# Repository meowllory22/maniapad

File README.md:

# maniapad
macropad for 4key rhythm games like osumania, quaver, etc ! :-) also its cat shaped because why not?

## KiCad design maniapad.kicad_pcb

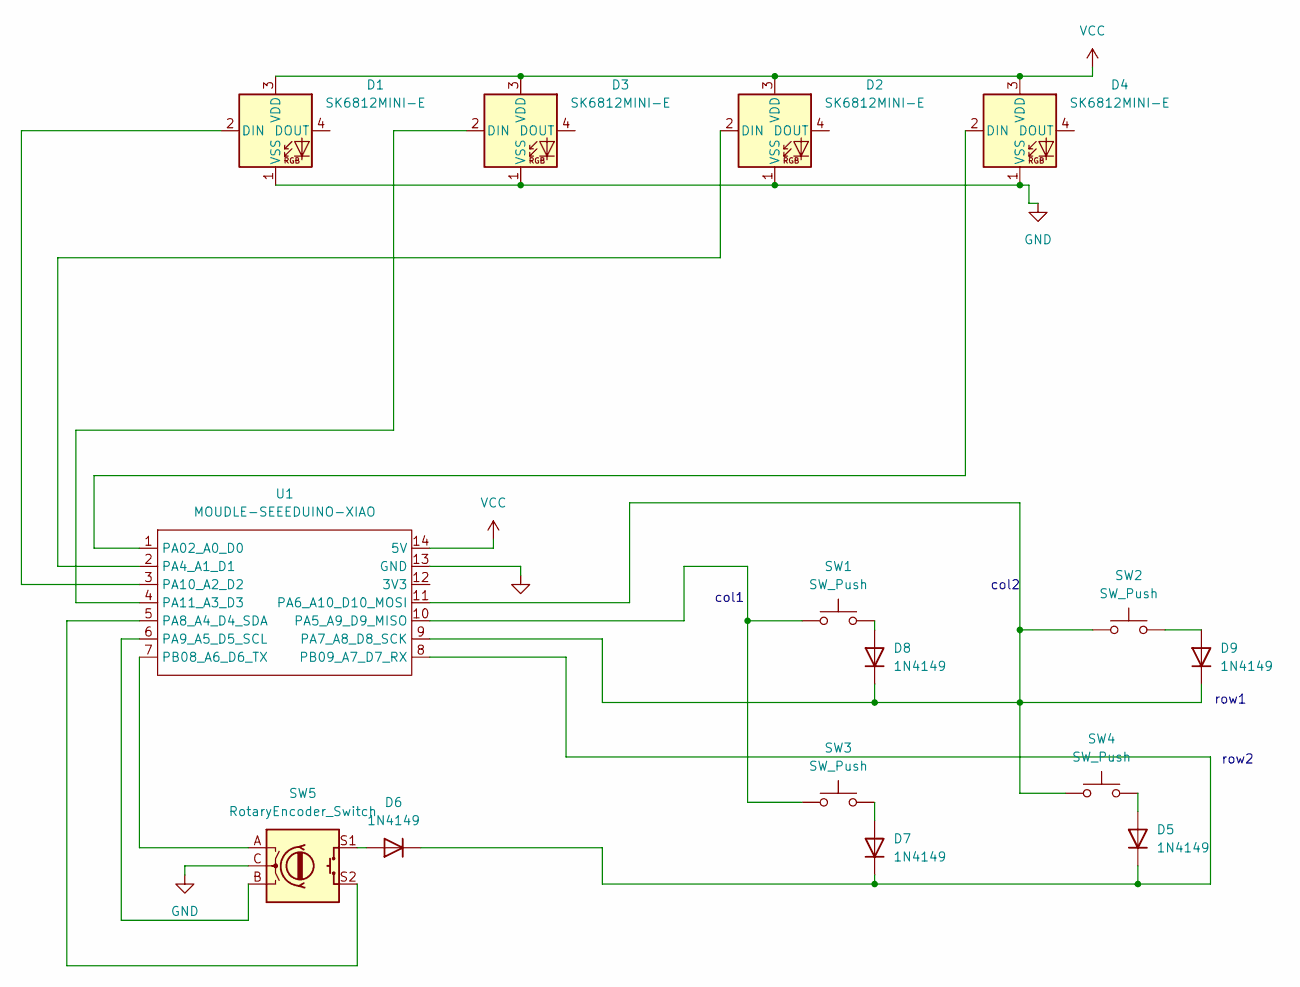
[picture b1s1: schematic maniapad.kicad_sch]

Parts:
D1, D2, D3, D4: SK6812MINI-E; LED_SK6812MINI-E_3.2x2.8mm_P1.5mm_ReverseMount
D5, D6, D7, D8, D9: 1N4149; D_DO-35_SOD27_P7.62mm_Horizontal
SW1, SW2, SW3, SW4: SW_Push; SW_Cherry_MX_1.00u_PCB
SW5: RotaryEncoder_Switch; RotaryEncoder_Alps_EC11E-Switch_Vertical_H20mm
U1: MOUDLE-SEEEDUINO-XIAO; XIAO-Generic-Hybrid-14P-2.54-21X17.8MM

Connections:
GND: D1.1 (VSS), D2.1 (VSS), D3.1 (VSS), D4.1 (VSS), SW5.C, U1.13 (GND)
unnamed: D1.2 (DIN), U1.3 (PA10_A2_D2)
unnamed: D2.2 (DIN), U1.2 (PA4_A1_D1)
unnamed: D3.2 (DIN), U1.4 (PA11_A3_D3)
unnamed: D4.2 (DIN), U1.1 (PA02_A0_D0)
unnamed: D5.2 (A), SW4.2
unnamed: D5.1 (K), D6.1 (K), D7.1 (K), U1.8 (PB09_A7_D7_RX)
unnamed: D6.2 (A), SW5.S1
unnamed: D7.2 (A), SW3.2
unnamed: D8.2 (A), SW1.2
unnamed: D8.1 (K), D9.1 (K), SW2.1, SW4.1, U1.9 (PA7_A8_D8_SCK), U1.11 (PA6_A10_D10_MOSI)
unnamed: D9.2 (A), SW2.2
unnamed: SW1.1, SW3.1, U1.10 (PA5_A9_D9_MISO)
unnamed: SW5.S2, U1.5 (PA8_A4_D4_SDA)
unnamed: SW5.B, U1.6 (PA9_A5_D5_SCL)
unnamed: SW5.A, U1.7 (PB08_A6_D6_TX)
VCC: D1.3 (VDD), D2.3 (VDD), D3.3 (VDD), D4.3 (VDD), U1.14 (5V)

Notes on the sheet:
row2
row1
col2
col1

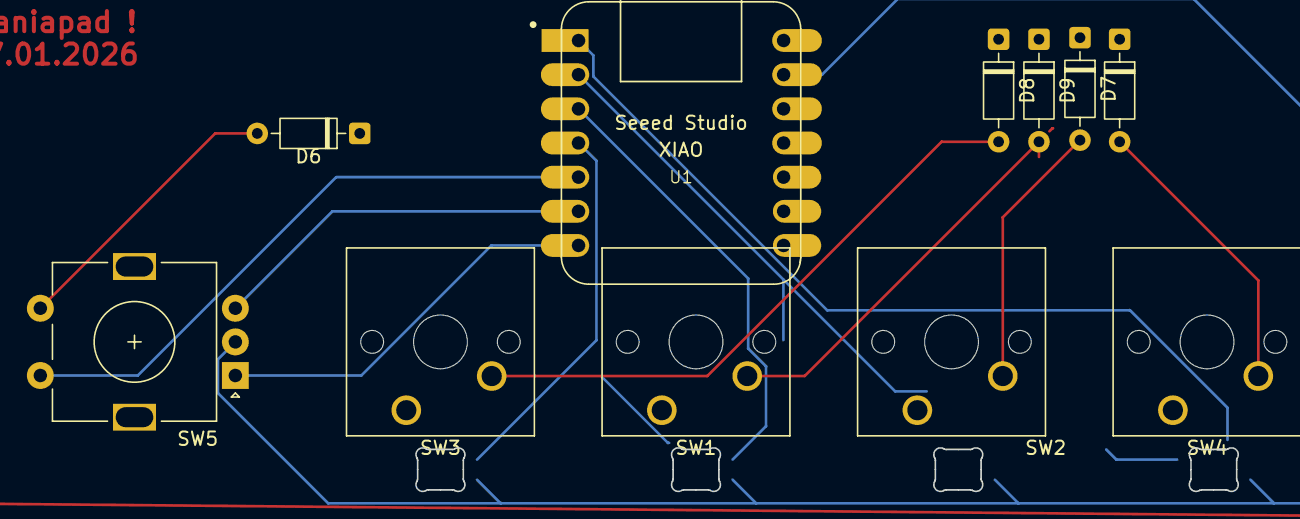
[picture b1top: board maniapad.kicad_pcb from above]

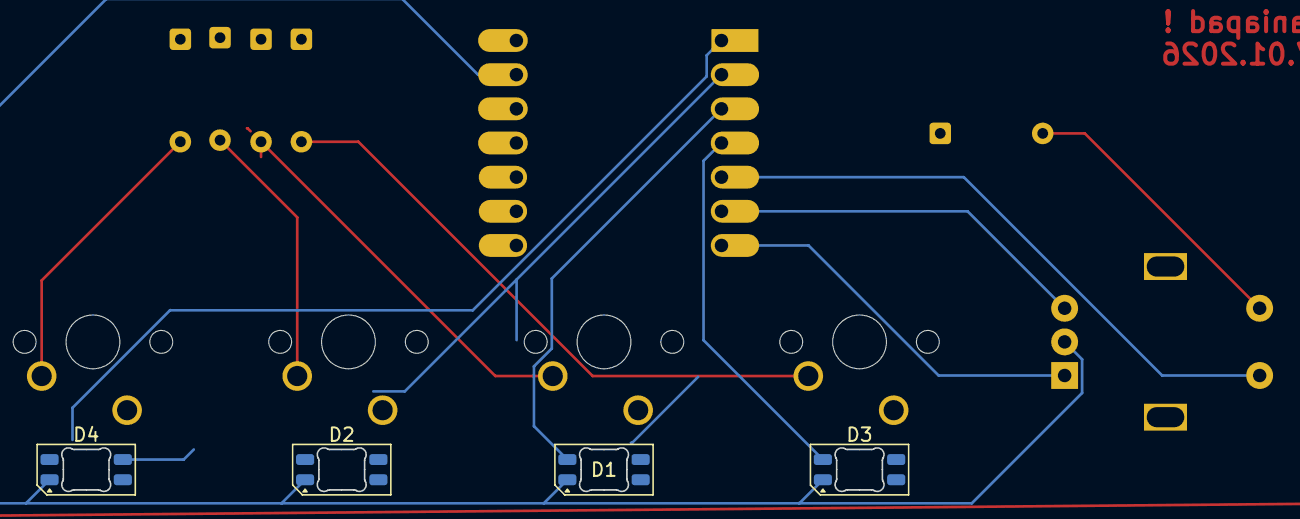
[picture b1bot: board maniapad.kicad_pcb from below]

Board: 2 copper layers, 15 parts (4 on the bottom side), 17 nets.

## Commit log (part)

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2026-06-30 Enhance README with cat shape detail
    Added a playful description about the cat shape of the macropad.
